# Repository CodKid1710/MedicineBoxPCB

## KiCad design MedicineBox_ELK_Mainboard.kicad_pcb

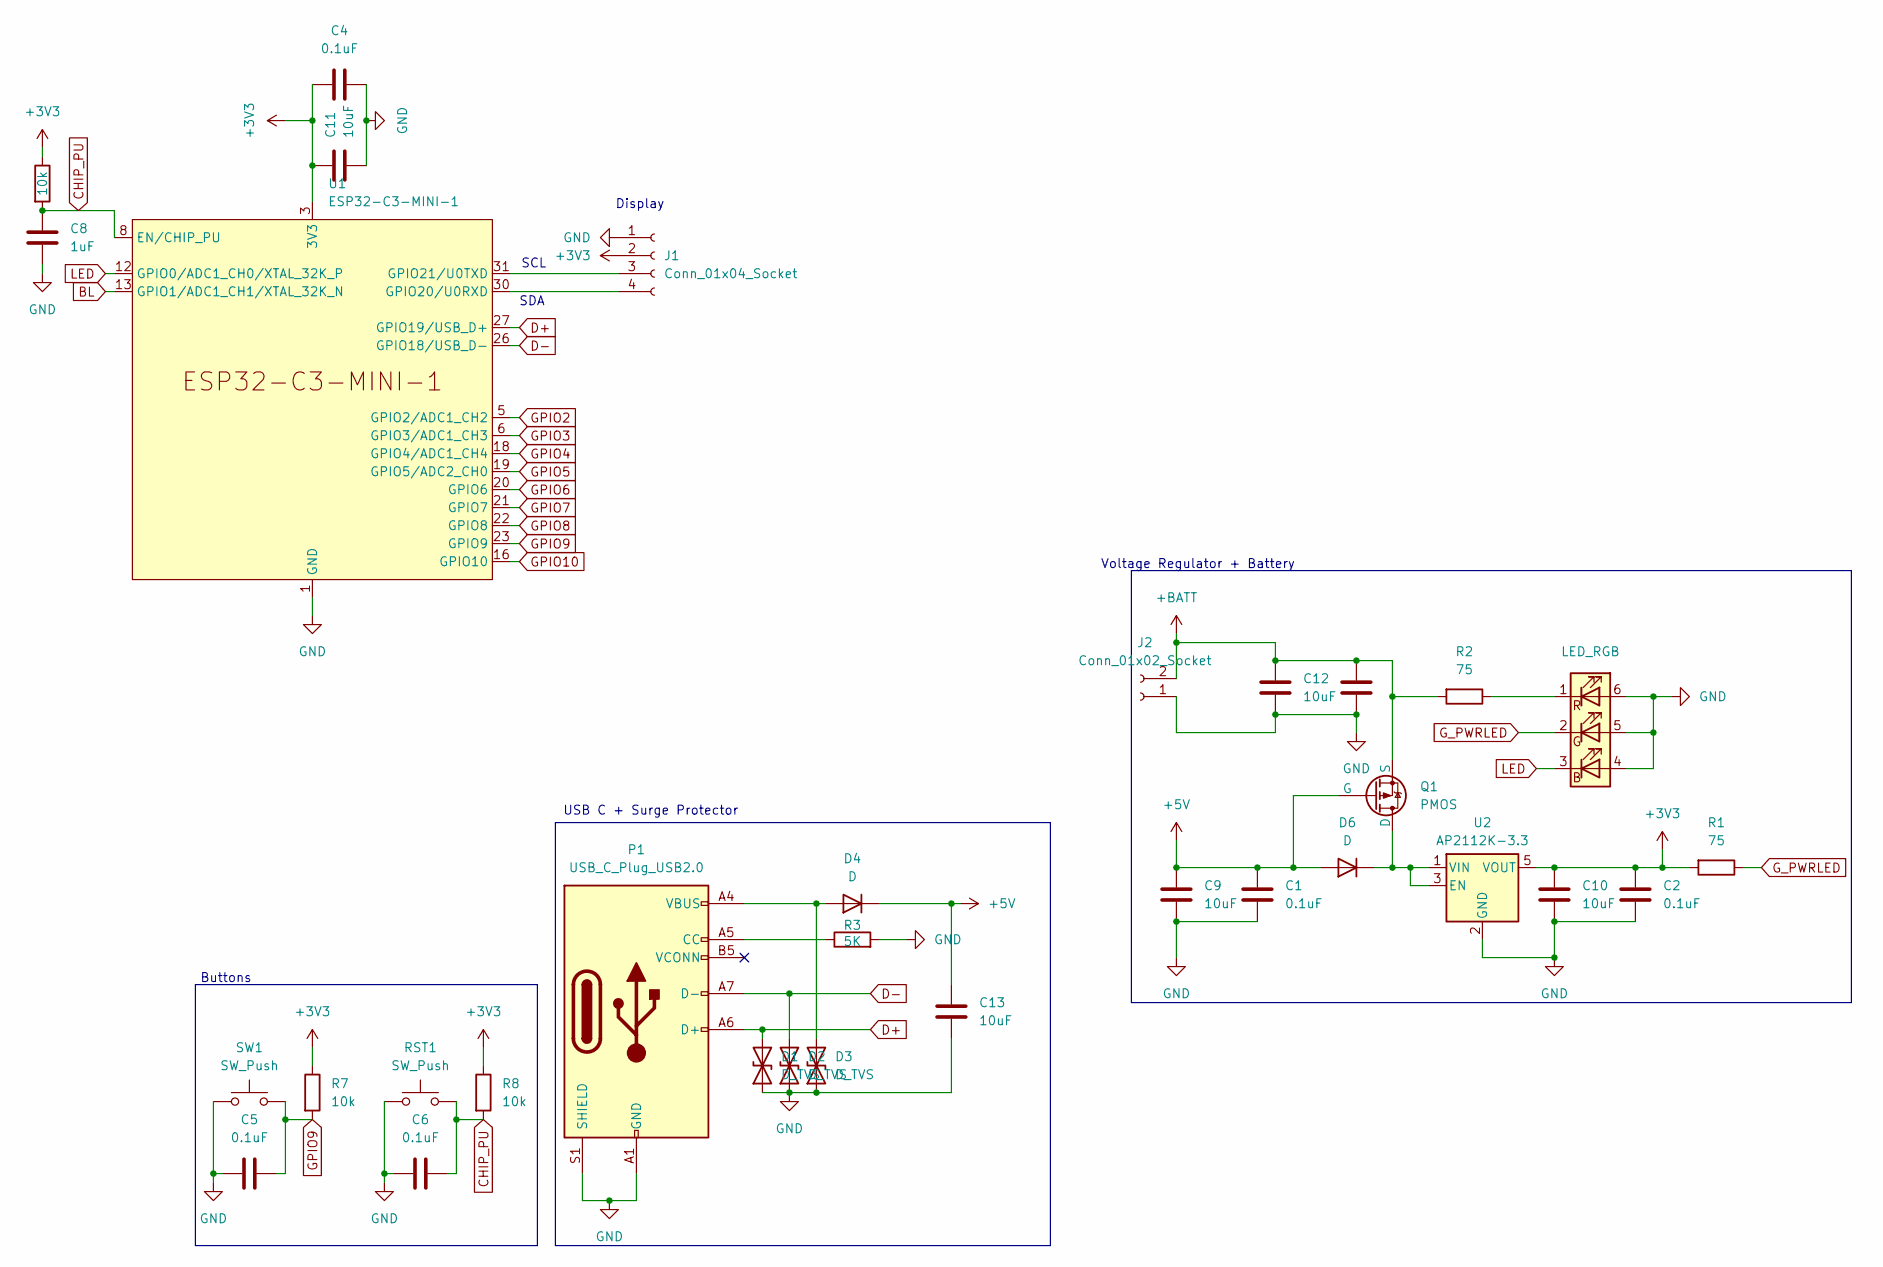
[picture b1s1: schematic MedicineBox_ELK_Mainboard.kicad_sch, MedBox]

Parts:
C1, C2, C4, C5, C6, C7: 0.1uF; C_0805_2012Metric
C8: 1uF; C_1206_3216Metric
C9, C10, C11, C12, C13: 10uF; C_1808_4520Metric
D1, D2, D3: D_TVS; D_1210_3225Metric
D4, D6: D; D_0805_2012Metric
D5: LED_RGB; LED_RGB_5050-6
J1: Conn_01x04_Socket; PinHeader_1x04_P2.54mm_Horizontal
J2: Conn_01x02_Socket; JST_EH_B2B-EH-A_1x02_P2.50mm_Vertical
P1: USB_C_Plug_USB2.0; USB_C_Receptacle_GCT_USB4105-xx-A_16P_TopMnt_Horizontal
Q1: PMOS; PQFN_8x8
R1, R2: 75; R_0805_2012Metric
R3: 5K; R_1206_3216Metric
R4, R7, R8: 10k; R_1812_4532Metric
RST1: SW_Push; SW_SPST_CK_RS282G05A3
SW1: SW_Push; SW_SPST_CK_RS282G05A3
U1: ESP32-C3-MINI-1
U2: AP2112K-3.3; SOT-23-5

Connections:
+3V3: C2.1, C4.1, C10.1, C11.1, J1.2, R1.2, R4.1, R7.1, R8.1, U1.3 (3V3), U2.5 (VOUT)
+5V: C1.1, C9.1, C13.1, D4.1 (K), D6.2 (A), Q1.2 (G)
+BATT: C7.1, C12.1, J2.2, Q1.3 (S), R2.2
BL: U1.13 (GPIO1/ADC1_CH1/XTAL_32K_N)
CHIP_PU: C6.2, C8.1, R4.2, R8.2, RST1.2, U1.8 (EN/CHIP_PU)
D+: D1.2 (A2), P1.A6 (D+), U1.27 (GPIO19/USB_D+)
D-: D2.2 (A2), P1.A7 (D-), U1.26 (GPIO18/USB_D-)
GND: C1.2, C2.2, C4.2, C5.1, C6.1, C7.2, C8.2, C9.2, C10.2, C11.2, C12.2, C13.2, D1.1 (A1), D2.1 (A1), D3.1 (A1), D5.4 (BA), D5.5 (GA), D5.6 (RA), J1.1, J2.1, P1.A1 (GND), P1.A12 (GND), P1.B1 (GND), P1.B12 (GND), P1.S1 (SHIELD), R3.2, RST1.1, SW1.1, U1.1 (GND), U1.2 (GND), U1.11 (GND), U1.14 (GND), U1.36 (GND), U1.37 (GND), U1.38 (GND), U1.39 (GND), U1.40 (GND), U1.41 (GND), U1.42 (GND), U1.43 (GND), U1.44 (GND), U1.45 (GND), U1.46 (GND), U1.47 (GND), U1.48 (GND), U1.49 (GND), U1.50 (GND), U1.51 (GND), U1.52 (GND), U1.53 (GND), U2.2 (GND)
GPIO2: U1.5 (GPIO2/ADC1_CH2)
GPIO3: U1.6 (GPIO3/ADC1_CH3)
GPIO4: U1.18 (GPIO4/ADC1_CH4)
GPIO5: U1.19 (GPIO5/ADC2_CH0)
GPIO6: U1.20 (GPIO6)
GPIO7: U1.21 (GPIO7)
GPIO8: U1.22 (GPIO8)
GPIO9: C5.2, R7.2, SW1.2, U1.23 (GPIO9)
GPIO10: U1.16 (GPIO10)
G_PWRLED: D5.2 (GK), R1.1
LED: D5.3 (BK), U1.12 (GPIO0/ADC1_CH0/XTAL_32K_P)
unnamed: D3.2 (A2), D4.2 (A), P1.A4 (VBUS), P1.A9 (VBUS), P1.B4 (VBUS), P1.B9 (VBUS)
unnamed: D5.1 (RK), R2.1
unnamed: D6.1 (K), Q1.1 (D), U2.1 (VIN), U2.3 (EN)
unnamed: J1.3, U1.31 (GPIO21/U0TXD)
unnamed: J1.4, U1.30 (GPIO20/U0RXD)
unnamed: P1.A5 (CC), R3.1

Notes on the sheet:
Buttons
Display
USB C + Surge Protector
SDA
Voltage Regulator + Battery
SCL

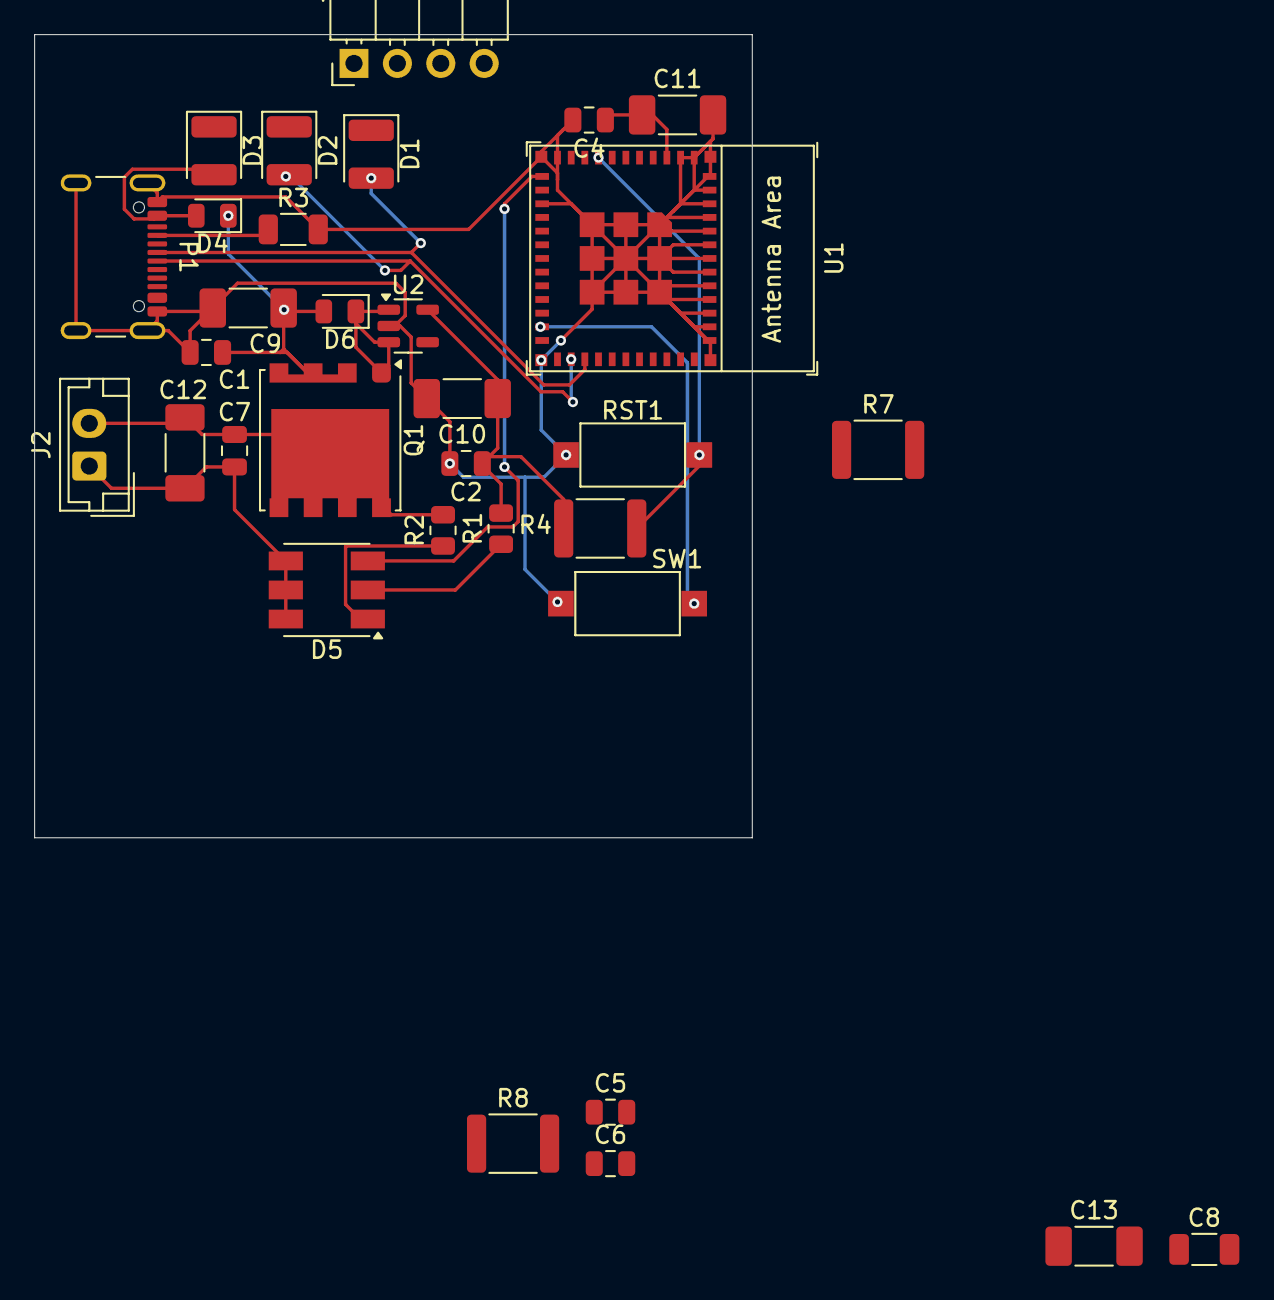
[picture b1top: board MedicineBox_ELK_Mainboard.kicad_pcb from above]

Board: 2 copper layers, 42.0 x 47.0 mm, 32 parts (0 on the bottom side), 16 nets.

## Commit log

2025-04-09 test
2025-04-09 added gitignore
